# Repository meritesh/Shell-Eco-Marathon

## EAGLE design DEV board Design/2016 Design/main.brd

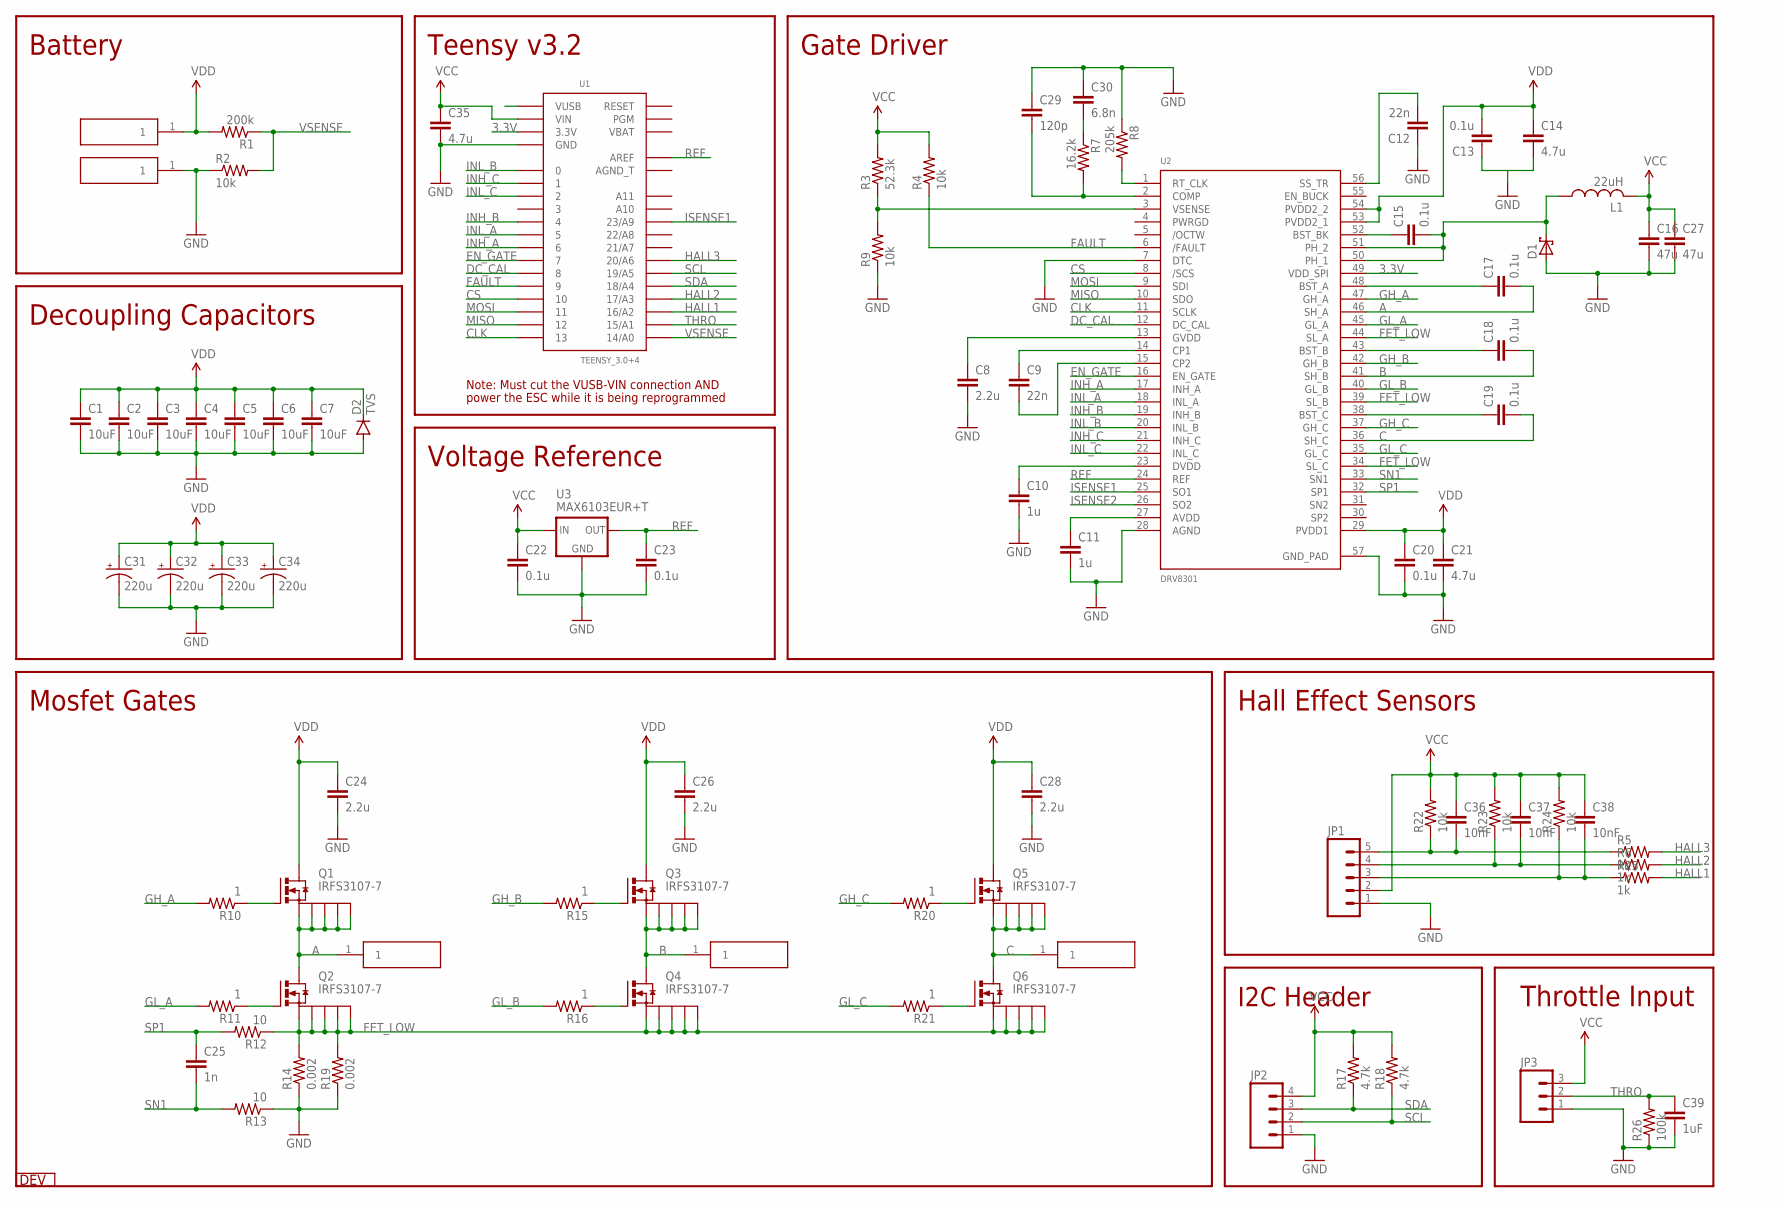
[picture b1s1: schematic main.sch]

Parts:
C1, C2, C3, C4, C5, C6, C7: 10uF; 1206
C8: 2.2u; 0603-CAP
C9, C12: 22n; 0603-CAP
C10, C11: 1u; 0603-CAP
C13, C15, C17, C18, C19, C20, C22, C23: 0.1u; 0603-CAP
C14, C21: 4.7u; 0805
C16, C27: 47u; 0805
C24, C26, C28: 2.2u; 1206
C25: 1n; 0603-CAP
C29: 120p; 0603-CAP
C30: 6.8n; 0603-CAP
C31, C32, C33, C34: 220u; E3,5-8
C35: 4.7u; 0603-CAP
C36, C37, C38: 10nF; 0603-CAP
C39: 1uF; 0603-CAP
D1: SCHOTTKY_SMA; SMA
D2: TVS; SMC
J1, J2, J3, J4, J5: 0.125_PAD
JP1: M05PTH; 1X05
JP2: M04PTH; 1X04
JP3: M03PTH; 1X03
L1: 22uH; L5650M
Q1, Q2, Q3, Q4, Q5, Q6: IRFS3107-7; D2PAK-7
R1: 200k; 0603-RES
R2, R4, R9, R22, R23, R24: 10k; 0603-RES
R3: 52.3k; 0603-RES
R5, R6, R25: 1k; 0603-RES
R7: 16.2k; 0603-RES
R8: 205k; 0603-RES
R10, R11, R15, R16, R20, R21: 1; 0603-RES
R12, R13: 10; 0603-RES
R14, R19: 0.002; R2512
R17, R18: 4.7k; 0603-RES
R26: 100k; 0603-RES
U1: TEENSY_3.0+4
U2: DRV8301
U3: MAX6103EUR+T; SOT23-3
U$16: DEV

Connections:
3.3V: U1.3.3V, U1.3.3V1 (3.3V), U2.49 (VDD_SPI)
A: C17.2, J3.1, Q1.S, Q1.S1, Q1.S2, Q1.S3, Q1.S4, Q2.D, U2.46 (SH_A)
AGND_T: U1.AGND_T
B: C18.2, J4.1, Q3.S, Q3.S1, Q3.S2, Q3.S3, Q3.S4, Q4.D, U2.41 (SH_B)
C: C19.2, J5.1, Q5.S, Q5.S1, Q5.S2, Q5.S3, Q5.S4, Q6.D, U2.36 (SH_C)
CLK: U1.13, U2.11 (SCLK)
CS: U1.10, U2.8 (/SCS)
DC_CAL: U1.8, U2.12 (DC_CAL)
EN_GATE: U1.7, U2.16 (EN_GATE)
FAULT: R4.1, U1.9, U2.6 (/FAULT)
FET_LOW: Q2.S, Q2.S1, Q2.S2, Q2.S3, Q2.S4, Q4.S, Q4.S1, Q4.S2, Q4.S3, Q4.S4, Q6.S, Q6.S1, Q6.S2, Q6.S3, Q6.S4, R12.1, R14.2, R19.2, U2.34 (SL_C), U2.39 (SL_B), U2.44 (SL_A)
GH_A: R10.2, U2.47 (GH_A)
GH_B: R15.2, U2.42 (GH_B)
GH_C: R20.2, U2.37 (GH_C)
GL_A: R11.2, U2.45 (GL_A)
GL_A': Q2.G, R11.1
GL_B: R16.2, U2.40 (GL_B)
GL_B': Q4.G, R16.1
GL_C: R21.2, U2.35 (GL_C)
GL_C': Q6.G, R21.1
GND: C1.2, C2.2, C3.2, C4.2, C5.2, C6.2, C7.2, C8.2, C10.2, C11.2, C12.1, C13.1, C14.2, C16.2, C20.2, C21.2, C22.2, C23.2, C24.2, C26.2, C27.2, C28.2, C29.1, C30.1, C31.-, C32.-, C33.-, C34.-, C35.2, C39.2, D1.A, D2.A, J2.1, JP1.1, JP2.1, JP3.1, R2.1, R8.1, R9.1, R13.1, R14.1, R19.1, R26.1, U1.GND, U1.GND1 (GND), U2.7 (DTC), U2.28 (AGND), U2.57 (GND_PAD), U3.3 (GND)
HALL1: R25.2, U1.16/A2
HALL2: R6.2, U1.17/A3
HALL3: R5.2, U1.20/A6
INH_A: U1.6, U2.17 (INH_A)
INH_B: U1.4, U2.19 (INH_B)
INH_C: U1.1, U2.21 (INH_C)
INL_A: U1.5, U2.18 (INL_A)
INL_B: U1.0, U2.20 (INL_B)
INL_C: U1.2, U2.22 (INL_C)
ISENSE1: U1.23/A9, U2.25 (SO1)
ISENSE2: U2.26 (SO2)
MISO: U1.12, U2.10 (SDO)
MOSI: U1.11, U2.9 (SDI)
unnamed: Q3.G, R15.1
unnamed: R3.1, R9.2, U2.3 (VSENSE)
unnamed: C29.2, R7.2, U2.2 (COMP)
unnamed: C10.1, U2.23 (DVDD)
unnamed: Q5.G, R20.1
unnamed: C12.2, U2.56 (SS_TR)
unnamed: C30.2, R7.1
unnamed: C15.1, U2.52 (BST_BK)
unnamed: Q1.G, R10.1
unnamed: R8.2, U2.1 (RT_CLK)
unnamed: C36.2, JP1.5, R5.1, R22.1
unnamed: C37.2, JP1.4, R6.1, R23.1
unnamed: C38.2, JP1.3, R24.1, R25.1
unnamed: C19.1, U2.38 (BST_C)
unnamed: C9.1, U2.14 (CP1)
unnamed: C11.1, U2.27 (AVDD)
unnamed: C9.2, U2.15 (CP2)
unnamed: C8.1, U2.13 (GVDD)
unnamed: C18.1, U2.43 (BST_B)
unnamed: C17.1, U2.48 (BST_A)
unnamed: C15.2, D1.C, L1.1, U2.50 (PH_1), U2.51 (PH_2)
REF: C23.1, U1.AREF, U2.24 (REF), U3.2 (OUT)
SCL: JP2.2, R18.1, U1.19/A5
SDA: JP2.3, R17.1, U1.18/A4
SN1: C25.2, R13.2, U2.33 (SN1)
SP1: C25.1, R12.2, U2.32 (SP1)
THRO: C39.1, JP3.2, R26.2, U1.15/A1
VBAT: U1.VBAT
VCC: C16.1, C22.1, C27.1, C35.1, C36.1, C37.1, C38.1, JP1.2, JP2.4, JP3.3, L1.2, R3.2, R4.2, R17.2, R18.2, R22.2, R23.2, R24.2, U1.VIN, U3.1 (IN)
VDD: C1.1, C2.1, C3.1, C4.1, C5.1, C6.1, C7.1, C13.2, C14.1, C20.1, C21.1, C24.1, C26.1, C28.1, C31.+, C32.+, C33.+, C34.+, D2.C, J1.1, Q1.D, Q3.D, Q5.D, R1.2, U2.29 (PVDD1), U2.53 (PVDD2_1), U2.54 (PVDD2_2)
VSENSE: R1.1, R2.2, U1.14/A0

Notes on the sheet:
Teensy v3.2
Gate Driver
Mosfet Gates
Battery
Voltage Reference
Hall Effect Sensors
Decoupling Capacitors
Note: Must cut the VUSB-VIN connection AND
power the ESC while it is being reprogrammed
Throttle Input
I2C Header

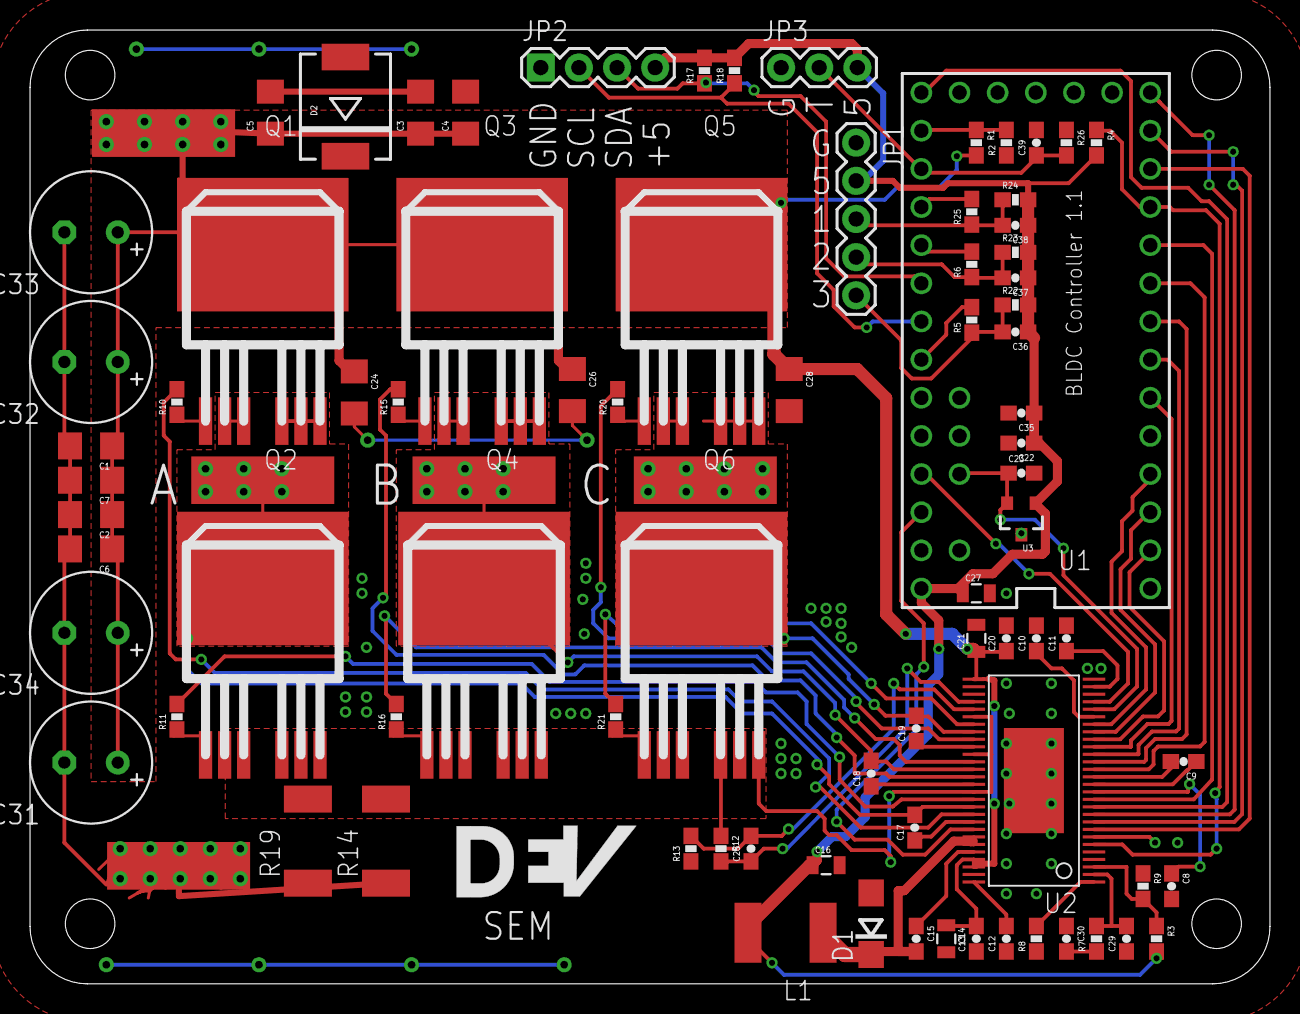
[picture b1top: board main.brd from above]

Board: 2 copper layers, 82.5 x 63.5 mm, 86 parts (0 on the bottom side), 62 nets.

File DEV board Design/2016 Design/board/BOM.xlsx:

Description | Digikey Part # | Value | Components | Price | Qty | Total |  | Grand total | 68.83
Teensy 3.2 | 1568-1231-ND |  | U1 | 22.5 | 1 | 22.5
DRV8301 | 296-29433-1-ND |  | U2 | 6.14 | 1 | 6.14
Voltage reference | MAX6103EUR+TCT-ND | 3v | U3 | 1.1399999999999999 | 1 | 1.1399999999999999
NFET | IRFS3107-7PPBF-ND |  | Q1 Q2 Q3 Q4 Q5 Q6 | 5.24 | 6 | 31.44
TVS | 497-6522-1-ND | 48V | D2 | 0.53 | 1 | 0.53
TVS | GSOT05-E3-08CT-ND | 5v | D3 | 0.38 | 1 | 0.38
 |  |  |  |  |  | 0
 |  |  |  |  |  | 0
Ceramic cap 50V 0603 | 490-1429-1-ND | 120pF | C29 | 0.01 | 1 | 0.01
Ceramic cap 50V 0603 | 399-1089-1-ND | 6.8nF | C30 | 0.01 | 1 | 0.01
Resistor 0603 | 311-16.2KHRCT-ND | 16.2k | R7 | 0.01 | 1 | 0.01
Resistor 0603 | 311-52.3KHRCT-ND | 52.3k | R3 | 0.01 | 1 | 0.01
Inductor | 587-2952-1-ND | 22uH | L1 | 0.43 | 1 | 0.43
Ceramic cap 6.3V 0805 | 311-1897-1-ND | 47uF | C16 C27 | 0.46 | 2 | 0.92
Schottkey diode | 641-1701-1-ND | 200V 3A | D1 | 0.43 | 1 | 0.43
Ceramic cap 16V 0603 | 490-3296-1-ND | 2.2uF | C8 | 0.1 | 1 | 0.1
Ceramic cap 50V 0603 | 490-1500-6-ND | 22nF | C9 C12 | 0.01 | 2 | 0.02
Ceramic cap 50V 0603 | 490-1519-6-ND | 0.1uF | C13 C15 C17 C18 C19 C20 C22 C23 | 0.01 | 8 | 0.08
Ceramic cap 25V 0805 | 490-3335-6-ND | 4.7uF | C14 C21 C35 | 0.1 | 3 | 0.30000000000000004
Ceramic cap 25V 0603 | 490-6339-6-ND | 10nF | C36 C37 C38 | 0.01 | 3 | 0.03
Resistor 0603 | 311-1.00KHRCT-ND | 1k | R5 R6 R25 | 0.01 | 3 | 0.03
Ceramic cap 50V 0603 | 587-3247-1-ND | 1uF | C10 C11 C39 | 0.12 | 3 | 0.36
Resistor 0603 | 311-4.70KHRCT-ND | 4.7k | R17 R18 | 0.01 | 2 | 0.02
Ceramic cap 50V 0603 | 478-1215-1-ND | 1nF | C25 | 0.01 | 1 | 0.01
Resistor 2512 | CSNL2512FT2L00DKR-ND | 2m | R14 R19 | 0.53 | 2 | 1.06
Resistor 0603 | 311-10.0HRCT-ND | 10 | R10 R11 R12 R13 R15 R16 R20 R21 | 0.01 | 8 | 0.08
Resistor 0603 | 311-10.0KHRCT-ND | 10k | R2 R4 R9 R22 R23 R24 | 0.01 | 6 | 0.06
Resistor 0603 | 311-205KHRCT-ND | 205k | R1 R8 R26 | 0.01 | 3 | 0.03
Ceramic cap 50V 1206 | 587-2994-1-ND | 4.7uF | C1 C2 C3 C4 C5 C6 C7 C24 C26 C28 | 0.15 | 10 | 1.5
Aluminum cap | 565-1604-ND | 180uF | C31 C32 C33 C34 | 0.3 | 4 | 1.2
 |  |  |  |  |  | 0
 |  |  |  |  |  | 0
 |  |  |  |  |  | 0
 |  |  |  |  |  | 0
 |  |  |  |  |  | 0
 |  |  |  |  |  | 0
 |  |  |  |  |  | 0
 |  |  |  |  |  | 0
 |  |  |  |  |  | 0
 |  |  |  |  |  | 0
 |  |  |  |  |  | 0
 |  |  |  |  |  | 0
 |  |  |  |  |  | 0
 |  |  |  |  |  | 0
 |  |  |  |  |  | 0
 |  |  |  |  |  | 0
 |  |  |  |  |  | 0
 |  |  |  |  |  | 0
 |  |  |  |  |  | 0

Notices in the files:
parts and their libraries:
SparkFun-Capacitors: Licensing: Creative Commons ShareAlike 4.0 International - https://creativecommons.org/licenses/by-sa/4.0
